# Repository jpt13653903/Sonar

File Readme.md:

# Sonar

Project used as a teaching aid for the [UCT FPGA course](https://github.com/jpt13653903/UCT-FPGA-Course).

## Overview

This DE10-Lite daughter card features transmitter and receiver array for a 10 kHz sonar system.

## Flexible Grid

The design features a 64-element grid of microphone sites and a connection matrix that supports 16 output channels.  The user can populate up to 16 microphones and then use the matrix to route them to the receiver channels.

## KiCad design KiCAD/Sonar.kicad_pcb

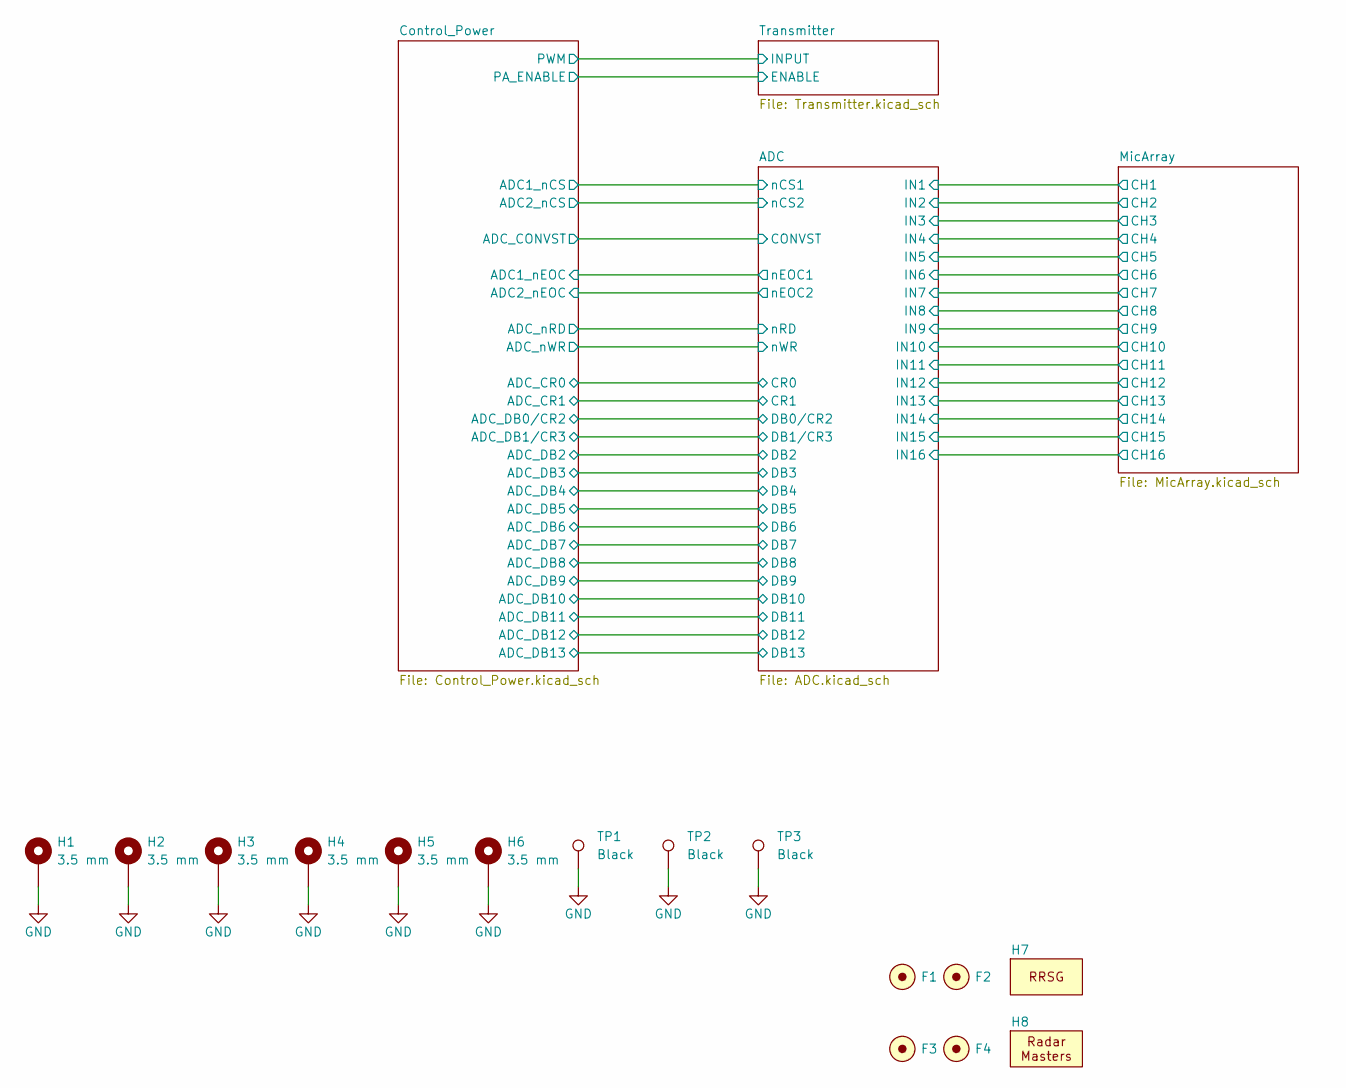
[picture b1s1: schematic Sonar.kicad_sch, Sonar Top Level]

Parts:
F1, F2, F3, F4: Fiducial_1mm_Mask3mm
H1, H2, H3, H4, H5, H6: MountingHole; MountingHole_3.5mm_Pad_Via
H7: RRSG
H8: RadarMasters
TP1, TP2, TP3: Keystone_5011_Black; TestPoint_Keystone_5010-5014_Multipurpose; MPN 5011

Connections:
GND: H1.1, H2.1, H3.1, H4.1, H5.1, H6.1, TP1.1 (1_1), TP2.1 (1_1), TP3.1 (1_1); also elsewhere on the board

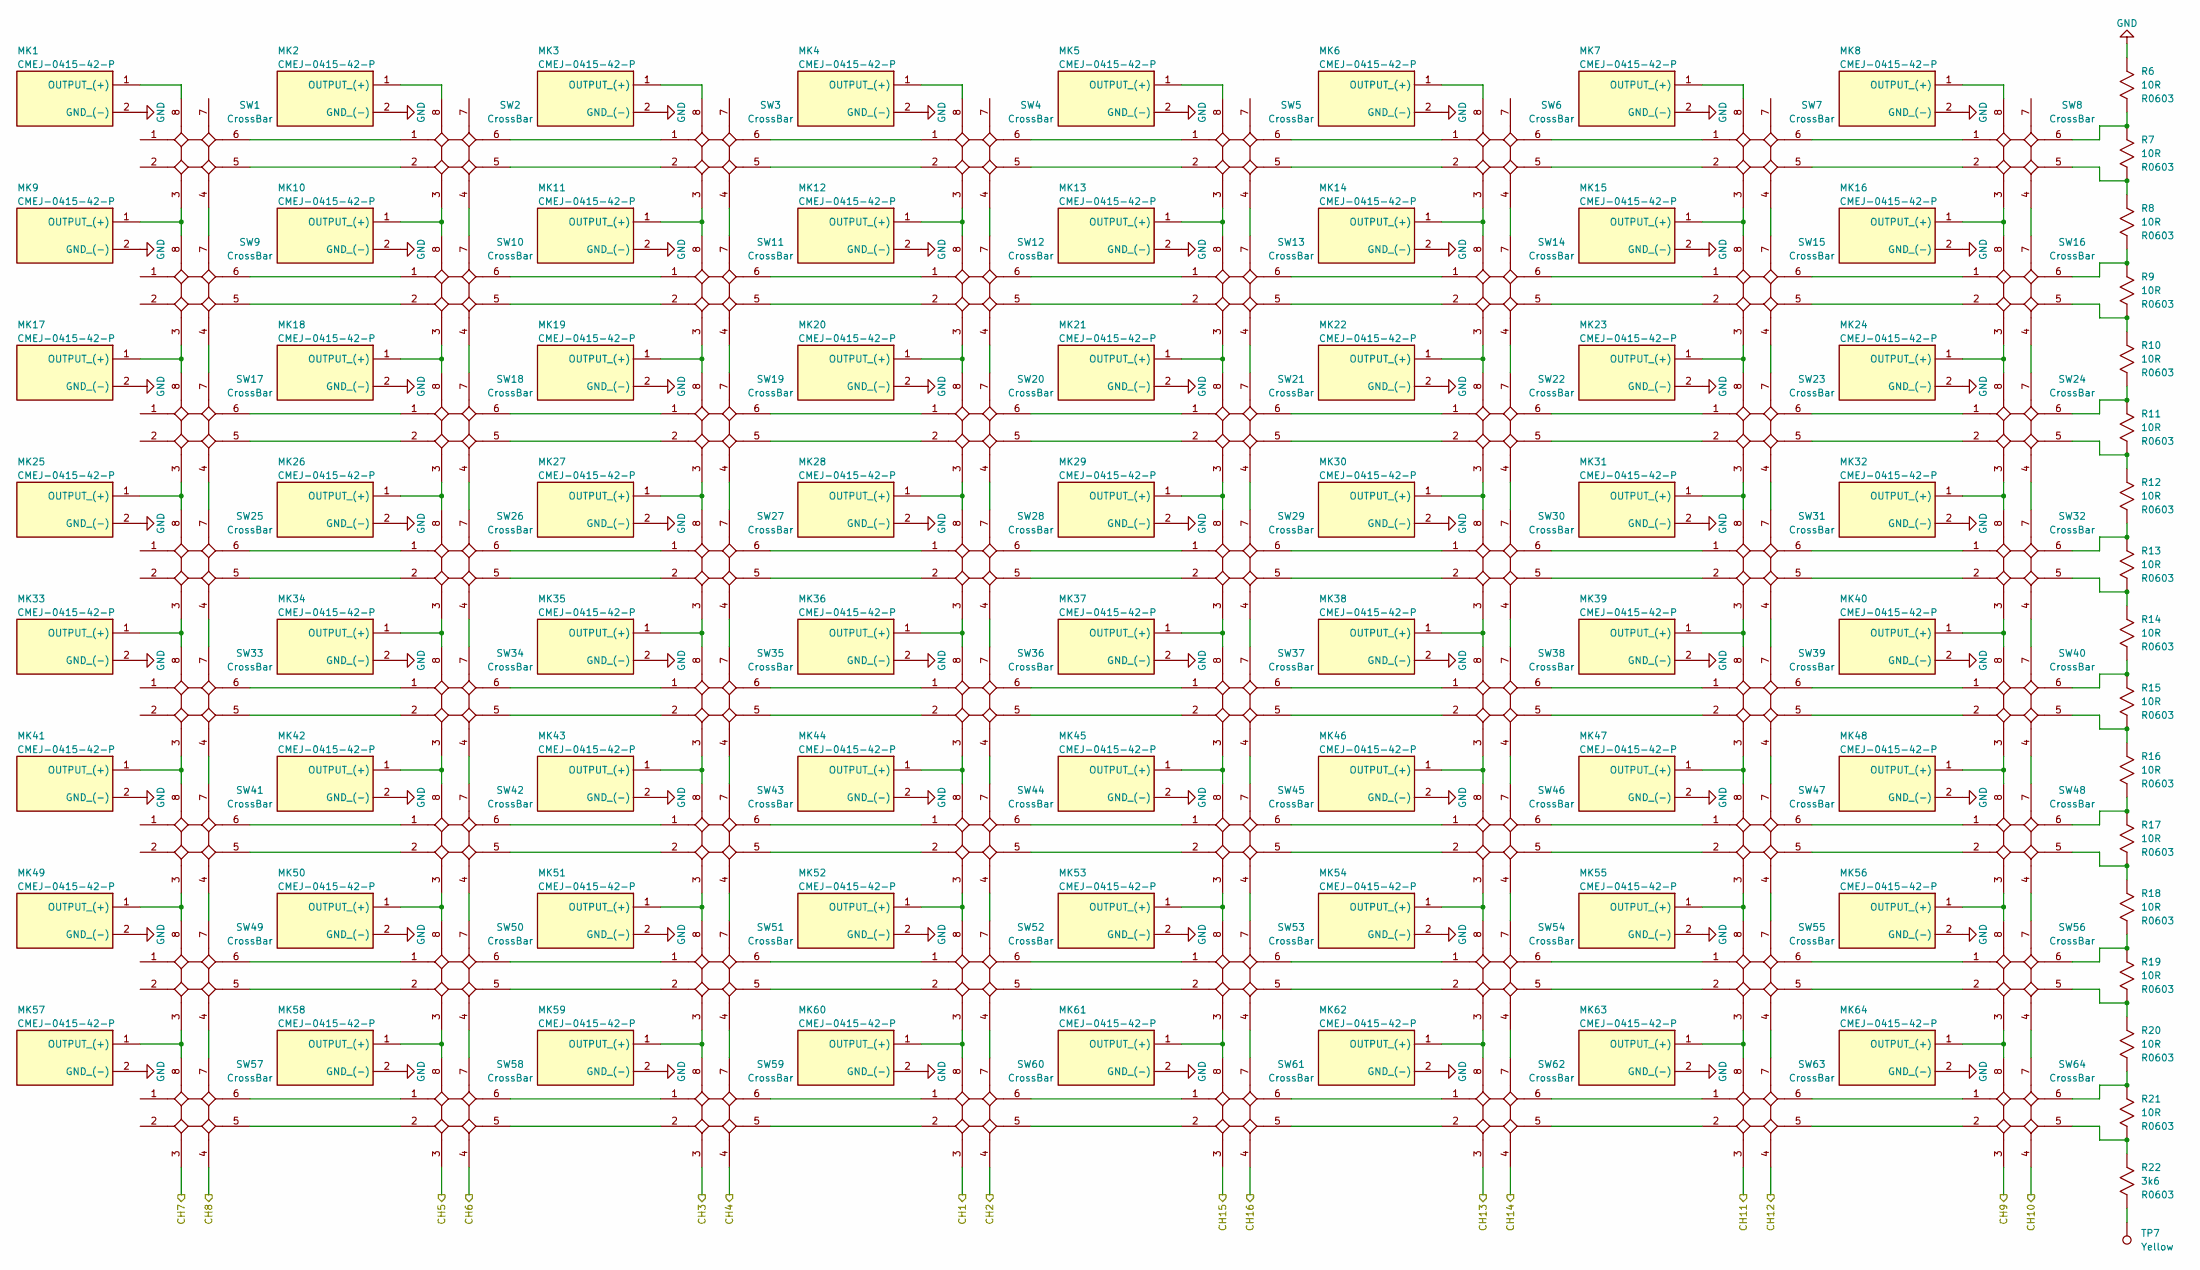
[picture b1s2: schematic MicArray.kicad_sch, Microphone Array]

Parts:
MK1, MK2, MK3, MK4, MK5, MK6, MK7, MK8, MK9, MK10, MK11, MK12, MK13, MK14, MK15, MK16, MK17, MK18, MK19, MK20, MK21, MK22, MK23, MK24, MK25, MK26, MK27, MK28, MK29, MK30, MK31, MK32, MK33, MK34, MK35, MK36, MK37, MK38, MK39, MK40, MK41, MK42, MK43, MK44, MK45, MK46, MK47, MK48, MK49, MK50, MK51, MK52, MK53, MK54, MK55, MK56, MK57, MK58, MK59, MK60, MK61, MK62, MK63, MK64: CMEJ-0415-42-P; CMEJ041542P; MPN CMEJ-0415-42-P
R6, R7, R8, R9, R10, R11, R12, R13, R14, R15, R16, R17, R18, R19, R20, R21: R0603_10R; R_0603_1608Metric; MPN CRGP0603F10R
R22: R0603_3k6; R_0603_1608Metric; MPN CRGP0603F3K6
SW1, SW2, SW3, SW4, SW5, SW6, SW7, SW8, SW9, SW10, SW11, SW12, SW13, SW14, SW15, SW16, SW17, SW18, SW19, SW20, SW21, SW22, SW23, SW24, SW25, SW26, SW27, SW28, SW29, SW30, SW31, SW32, SW33, SW34, SW35, SW36, SW37, SW38, SW39, SW40, SW41, SW42, SW43, SW44, SW45, SW46, SW47, SW48, SW49, SW50, SW51, SW52, SW53, SW54, SW55, SW56, SW57, SW58, SW59, SW60, SW61, SW62, SW63, SW64: CrossBar; CrossBar_2x2
TP7: Keystone_5014_Yellow; TestPoint_Keystone_5010-5014_Multipurpose; MPN 5014

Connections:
/ADC/IN1: SW60.3 (OUTPUT_(+)); also elsewhere on the board
/ADC/IN2: SW60.4 (GND_(-)); also elsewhere on the board
/ADC/IN3: SW59.3 (OUTPUT_(+)); also elsewhere on the board
/ADC/IN4: SW59.4 (GND_(-)); also elsewhere on the board
/ADC/IN5: SW58.3 (OUTPUT_(+)); also elsewhere on the board
/ADC/IN6: SW58.4 (GND_(-)); also elsewhere on the board
/ADC/IN7: SW57.3 (OUTPUT_(+)); also elsewhere on the board
/ADC/IN8: SW57.4 (GND_(-)); also elsewhere on the board
/ADC/IN9: SW64.3 (OUTPUT_(+)); also elsewhere on the board
/ADC/IN10: SW64.4 (GND_(-)); also elsewhere on the board
/ADC/IN11: SW63.3 (OUTPUT_(+)); also elsewhere on the board
/ADC/IN12: SW63.4 (GND_(-)); also elsewhere on the board
/ADC/IN13: SW62.3 (OUTPUT_(+)); also elsewhere on the board
/ADC/IN14: SW62.4 (GND_(-)); also elsewhere on the board
/ADC/IN15: SW61.3 (OUTPUT_(+)); also elsewhere on the board
/ADC/IN16: SW61.4 (GND_(-)); also elsewhere on the board
GND: MK1.2 (GND_(-)), MK2.2 (GND_(-)), MK3.2 (GND_(-)), MK4.2 (GND_(-)), MK5.2 (GND_(-)), MK6.2 (GND_(-)), MK7.2 (GND_(-)), MK8.2 (GND_(-)), MK9.2 (GND_(-)), MK10.2 (GND_(-)), MK11.2 (GND_(-)), MK12.2 (GND_(-)), MK13.2 (GND_(-)), MK14.2 (GND_(-)), MK15.2 (GND_(-)), MK16.2 (GND_(-)), MK17.2 (GND_(-)), MK18.2 (GND_(-)), MK19.2 (GND_(-)), MK20.2 (GND_(-)), MK21.2 (GND_(-)), MK22.2 (GND_(-)), MK23.2 (GND_(-)), MK24.2 (GND_(-)), MK25.2 (GND_(-)), MK26.2 (GND_(-)), MK27.2 (GND_(-)), MK28.2 (GND_(-)), MK29.2 (GND_(-)), MK30.2 (GND_(-)), MK31.2 (GND_(-)), MK32.2 (GND_(-)), MK33.2 (GND_(-)), MK34.2 (GND_(-)), MK35.2 (GND_(-)), MK36.2 (GND_(-)), MK37.2 (GND_(-)), MK38.2 (GND_(-)), MK39.2 (GND_(-)), MK40.2 (GND_(-)), MK41.2 (GND_(-)), MK42.2 (GND_(-)), MK43.2 (GND_(-)), MK44.2 (GND_(-)), MK45.2 (GND_(-)), MK46.2 (GND_(-)), MK47.2 (GND_(-)), MK48.2 (GND_(-)), MK49.2 (GND_(-)), MK50.2 (GND_(-)), MK51.2 (GND_(-)), MK52.2 (GND_(-)), MK53.2 (GND_(-)), MK54.2 (GND_(-)), MK55.2 (GND_(-)), MK56.2 (GND_(-)), MK57.2 (GND_(-)), MK58.2 (GND_(-)), MK59.2 (GND_(-)), MK60.2 (GND_(-)), MK61.2 (GND_(-)), MK62.2 (GND_(-)), MK63.2 (GND_(-)), MK64.2 (GND_(-)), R6.1; also elsewhere on the board
unnamed: MK1.1 (OUTPUT_(+)), SW1.8 (OUTPUT_(+))
unnamed: MK2.1 (OUTPUT_(+)), SW2.8 (OUTPUT_(+))
unnamed: MK3.1 (OUTPUT_(+)), SW3.8 (OUTPUT_(+))
unnamed: MK4.1 (OUTPUT_(+)), SW4.8 (OUTPUT_(+))
unnamed: MK5.1 (OUTPUT_(+)), SW5.8 (OUTPUT_(+))
unnamed: MK6.1 (OUTPUT_(+)), SW6.8 (OUTPUT_(+))
unnamed: MK7.1 (OUTPUT_(+)), SW7.8 (OUTPUT_(+))
unnamed: MK8.1 (OUTPUT_(+)), SW8.8 (OUTPUT_(+))
unnamed: MK9.1 (OUTPUT_(+)), SW1.3 (OUTPUT_(+)), SW9.8 (OUTPUT_(+))
unnamed: MK10.1 (OUTPUT_(+)), SW2.3 (OUTPUT_(+)), SW10.8 (OUTPUT_(+))
unnamed: MK11.1 (OUTPUT_(+)), SW3.3 (OUTPUT_(+)), SW11.8 (OUTPUT_(+))
unnamed: MK12.1 (OUTPUT_(+)), SW4.3 (OUTPUT_(+)), SW12.8 (OUTPUT_(+))
unnamed: MK13.1 (OUTPUT_(+)), SW5.3 (OUTPUT_(+)), SW13.8 (OUTPUT_(+))
unnamed: MK14.1 (OUTPUT_(+)), SW6.3 (OUTPUT_(+)), SW14.8 (OUTPUT_(+))
unnamed: MK15.1 (OUTPUT_(+)), SW7.3 (OUTPUT_(+)), SW15.8 (OUTPUT_(+))
unnamed: MK16.1 (OUTPUT_(+)), SW8.3 (OUTPUT_(+)), SW16.8 (OUTPUT_(+))
unnamed: MK17.1 (OUTPUT_(+)), SW9.3 (OUTPUT_(+)), SW17.8 (OUTPUT_(+))
unnamed: MK18.1 (OUTPUT_(+)), SW10.3 (OUTPUT_(+)), SW18.8 (OUTPUT_(+))
unnamed: MK19.1 (OUTPUT_(+)), SW11.3 (OUTPUT_(+)), SW19.8 (OUTPUT_(+))
unnamed: MK20.1 (OUTPUT_(+)), SW12.3 (OUTPUT_(+)), SW20.8 (OUTPUT_(+))
unnamed: MK21.1 (OUTPUT_(+)), SW13.3 (OUTPUT_(+)), SW21.8 (OUTPUT_(+))
unnamed: MK22.1 (OUTPUT_(+)), SW14.3 (OUTPUT_(+)), SW22.8 (OUTPUT_(+))
unnamed: MK23.1 (OUTPUT_(+)), SW15.3 (OUTPUT_(+)), SW23.8 (OUTPUT_(+))
unnamed: MK24.1 (OUTPUT_(+)), SW16.3 (OUTPUT_(+)), SW24.8 (OUTPUT_(+))
unnamed: MK25.1 (OUTPUT_(+)), SW17.3 (OUTPUT_(+)), SW25.8 (OUTPUT_(+))
unnamed: MK26.1 (OUTPUT_(+)), SW18.3 (OUTPUT_(+)), SW26.8 (OUTPUT_(+))
unnamed: MK27.1 (OUTPUT_(+)), SW19.3 (OUTPUT_(+)), SW27.8 (OUTPUT_(+))
unnamed: MK28.1 (OUTPUT_(+)), SW20.3 (OUTPUT_(+)), SW28.8 (OUTPUT_(+))
unnamed: MK29.1 (OUTPUT_(+)), SW21.3 (OUTPUT_(+)), SW29.8 (OUTPUT_(+))
unnamed: MK30.1 (OUTPUT_(+)), SW22.3 (OUTPUT_(+)), SW30.8 (OUTPUT_(+))
unnamed: MK31.1 (OUTPUT_(+)), SW23.3 (OUTPUT_(+)), SW31.8 (OUTPUT_(+))
unnamed: MK32.1 (OUTPUT_(+)), SW24.3 (OUTPUT_(+)), SW32.8 (OUTPUT_(+))
unnamed: MK33.1 (OUTPUT_(+)), SW25.3 (OUTPUT_(+)), SW33.8 (OUTPUT_(+))
unnamed: MK34.1 (OUTPUT_(+)), SW26.3 (OUTPUT_(+)), SW34.8 (OUTPUT_(+))
unnamed: MK35.1 (OUTPUT_(+)), SW27.3 (OUTPUT_(+)), SW35.8 (OUTPUT_(+))
unnamed: MK36.1 (OUTPUT_(+)), SW28.3 (OUTPUT_(+)), SW36.8 (OUTPUT_(+))
unnamed: MK37.1 (OUTPUT_(+)), SW29.3 (OUTPUT_(+)), SW37.8 (OUTPUT_(+))
unnamed: MK38.1 (OUTPUT_(+)), SW30.3 (OUTPUT_(+)), SW38.8 (OUTPUT_(+))
unnamed: MK39.1 (OUTPUT_(+)), SW31.3 (OUTPUT_(+)), SW39.8 (OUTPUT_(+))
unnamed: MK40.1 (OUTPUT_(+)), SW32.3 (OUTPUT_(+)), SW40.8 (OUTPUT_(+))
unnamed: MK41.1 (OUTPUT_(+)), SW33.3 (OUTPUT_(+)), SW41.8 (OUTPUT_(+))
unnamed: MK42.1 (OUTPUT_(+)), SW34.3 (OUTPUT_(+)), SW42.8 (OUTPUT_(+))
unnamed: MK43.1 (OUTPUT_(+)), SW35.3 (OUTPUT_(+)), SW43.8 (OUTPUT_(+))
unnamed: MK44.1 (OUTPUT_(+)), SW36.3 (OUTPUT_(+)), SW44.8 (OUTPUT_(+))
unnamed: MK45.1 (OUTPUT_(+)), SW37.3 (OUTPUT_(+)), SW45.8 (OUTPUT_(+))
unnamed: MK46.1 (OUTPUT_(+)), SW38.3 (OUTPUT_(+)), SW46.8 (OUTPUT_(+))
unnamed: MK47.1 (OUTPUT_(+)), SW39.3 (OUTPUT_(+)), SW47.8 (OUTPUT_(+))
unnamed: MK48.1 (OUTPUT_(+)), SW40.3 (OUTPUT_(+)), SW48.8 (OUTPUT_(+))
unnamed: MK49.1 (OUTPUT_(+)), SW41.3 (OUTPUT_(+)), SW49.8 (OUTPUT_(+))
unnamed: MK50.1 (OUTPUT_(+)), SW42.3 (OUTPUT_(+)), SW50.8 (OUTPUT_(+))
unnamed: MK51.1 (OUTPUT_(+)), SW43.3 (OUTPUT_(+)), SW51.8 (OUTPUT_(+))
unnamed: MK52.1 (OUTPUT_(+)), SW44.3 (OUTPUT_(+)), SW52.8 (OUTPUT_(+))
unnamed: MK53.1 (OUTPUT_(+)), SW45.3 (OUTPUT_(+)), SW53.8 (OUTPUT_(+))
unnamed: MK54.1 (OUTPUT_(+)), SW46.3 (OUTPUT_(+)), SW54.8 (OUTPUT_(+))
unnamed: MK55.1 (OUTPUT_(+)), SW47.3 (OUTPUT_(+)), SW55.8 (OUTPUT_(+))
unnamed: MK56.1 (OUTPUT_(+)), SW48.3 (OUTPUT_(+)), SW56.8 (OUTPUT_(+))
unnamed: MK57.1 (OUTPUT_(+)), SW49.3 (OUTPUT_(+)), SW57.8 (OUTPUT_(+))
unnamed: MK58.1 (OUTPUT_(+)), SW50.3 (OUTPUT_(+)), SW58.8 (OUTPUT_(+))
unnamed: MK59.1 (OUTPUT_(+)), SW51.3 (OUTPUT_(+)), SW59.8 (OUTPUT_(+))
unnamed: MK60.1 (OUTPUT_(+)), SW52.3 (OUTPUT_(+)), SW60.8 (OUTPUT_(+))
unnamed: MK61.1 (OUTPUT_(+)), SW53.3 (OUTPUT_(+)), SW61.8 (OUTPUT_(+))
unnamed: MK62.1 (OUTPUT_(+)), SW54.3 (OUTPUT_(+)), SW62.8 (OUTPUT_(+))
unnamed: MK63.1 (OUTPUT_(+)), SW55.3 (OUTPUT_(+)), SW63.8 (OUTPUT_(+))
unnamed: MK64.1 (OUTPUT_(+)), SW56.3 (OUTPUT_(+)), SW64.8 (OUTPUT_(+))
unnamed: R6.2, R7.1, SW8.6 (OUTPUT_(+))
unnamed: R7.2, R8.1, SW8.5 (GND_(-))
unnamed: R8.2, R9.1, SW16.6 (OUTPUT_(+))
unnamed: R9.2, R10.1, SW16.5 (GND_(-))
unnamed: R10.2, R11.1, SW24.6 (OUTPUT_(+))
unnamed: R11.2, R12.1, SW24.5 (GND_(-))
unnamed: R12.2, R13.1, SW32.6 (OUTPUT_(+))
unnamed: R13.2, R14.1, SW32.5 (GND_(-))
unnamed: R14.2, R15.1, SW40.6 (OUTPUT_(+))
unnamed: R15.2, R16.1, SW40.5 (GND_(-))
unnamed: R16.2, R17.1, SW48.6 (OUTPUT_(+))
unnamed: R17.2, R18.1, SW48.5 (GND_(-))
unnamed: R18.2, R19.1, SW56.6 (OUTPUT_(+))
unnamed: R19.2, R20.1, SW56.5 (GND_(-))
unnamed: R20.2, R21.1, SW64.6 (OUTPUT_(+))
unnamed: R21.2, R22.1, SW64.5 (GND_(-))
unnamed: R22.2, TP7.1 (1_1)
unnamed: SW1.4 (GND_(-)), SW9.7 (GND_(-))
unnamed: SW1.5 (GND_(-)), SW2.2 (GND_(-))
unnamed: SW1.6 (OUTPUT_(+)), SW2.1 (OUTPUT_(+))
unnamed: SW2.5 (GND_(-)), SW3.2 (GND_(-))
unnamed: SW2.6 (OUTPUT_(+)), SW3.1 (OUTPUT_(+))
unnamed: SW3.5 (GND_(-)), SW4.2 (GND_(-))
unnamed: SW3.6 (OUTPUT_(+)), SW4.1 (OUTPUT_(+))
unnamed: SW4.5 (GND_(-)), SW5.2 (GND_(-))
unnamed: SW4.6 (OUTPUT_(+)), SW5.1 (OUTPUT_(+))
unnamed: SW5.5 (GND_(-)), SW6.2 (GND_(-))
unnamed: SW5.6 (OUTPUT_(+)), SW6.1 (OUTPUT_(+))
unnamed: SW6.5 (GND_(-)), SW7.2 (GND_(-))
unnamed: SW6.6 (OUTPUT_(+)), SW7.1 (OUTPUT_(+))
unnamed: SW7.5 (GND_(-)), SW8.2 (GND_(-))
unnamed: SW7.6 (OUTPUT_(+)), SW8.1 (OUTPUT_(+))
unnamed: SW9.5 (GND_(-)), SW10.2 (GND_(-))
unnamed: SW10.4 (GND_(-)), SW18.7 (GND_(-))
unnamed: SW10.5 (GND_(-)), SW11.2 (GND_(-))
unnamed: SW2.4 (GND_(-)), SW10.7 (GND_(-))
unnamed: SW9.6 (OUTPUT_(+)), SW10.1 (OUTPUT_(+))
unnamed: SW10.6 (OUTPUT_(+)), SW11.1 (OUTPUT_(+))
unnamed: SW11.4 (GND_(-)), SW19.7 (GND_(-))
unnamed: SW11.5 (GND_(-)), SW12.2 (GND_(-))
unnamed: SW3.4 (GND_(-)), SW11.7 (GND_(-))
unnamed: SW11.6 (OUTPUT_(+)), SW12.1 (OUTPUT_(+))
unnamed: SW12.4 (GND_(-)), SW20.7 (GND_(-))
unnamed: SW12.5 (GND_(-)), SW13.2 (GND_(-))
unnamed: SW4.4 (GND_(-)), SW12.7 (GND_(-))
unnamed: SW12.6 (OUTPUT_(+)), SW13.1 (OUTPUT_(+))
unnamed: SW13.4 (GND_(-)), SW21.7 (GND_(-))
unnamed: SW13.5 (GND_(-)), SW14.2 (GND_(-))
unnamed: SW5.4 (GND_(-)), SW13.7 (GND_(-))
unnamed: SW13.6 (OUTPUT_(+)), SW14.1 (OUTPUT_(+))
unnamed: SW14.4 (GND_(-)), SW22.7 (GND_(-))
unnamed: SW14.5 (GND_(-)), SW15.2 (GND_(-))
unnamed: SW6.4 (GND_(-)), SW14.7 (GND_(-))
unnamed: SW14.6 (OUTPUT_(+)), SW15.1 (OUTPUT_(+))
unnamed: SW15.4 (GND_(-)), SW23.7 (GND_(-))
unnamed: SW15.5 (GND_(-)), SW16.2 (GND_(-))
unnamed: SW7.4 (GND_(-)), SW15.7 (GND_(-))
unnamed: SW15.6 (OUTPUT_(+)), SW16.1 (OUTPUT_(+))
unnamed: SW16.4 (GND_(-)), SW24.7 (GND_(-))
unnamed: SW8.4 (GND_(-)), SW16.7 (GND_(-))
unnamed: SW17.4 (GND_(-)), SW25.7 (GND_(-))
unnamed: SW17.5 (GND_(-)), SW18.2 (GND_(-))
unnamed: SW9.4 (GND_(-)), SW17.7 (GND_(-))
unnamed: SW17.6 (OUTPUT_(+)), SW18.1 (OUTPUT_(+))
unnamed: SW18.4 (GND_(-)), SW26.7 (GND_(-))
unnamed: SW18.5 (GND_(-)), SW19.2 (GND_(-))
unnamed: SW18.6 (OUTPUT_(+)), SW19.1 (OUTPUT_(+))
unnamed: SW19.4 (GND_(-)), SW27.7 (GND_(-))
unnamed: SW19.5 (GND_(-)), SW20.2 (GND_(-))
unnamed: SW19.6 (OUTPUT_(+)), SW20.1 (OUTPUT_(+))
unnamed: SW20.4 (GND_(-)), SW28.7 (GND_(-))
unnamed: SW20.5 (GND_(-)), SW21.2 (GND_(-))
unnamed: SW20.6 (OUTPUT_(+)), SW21.1 (OUTPUT_(+))
unnamed: SW21.4 (GND_(-)), SW29.7 (GND_(-))
unnamed: SW21.5 (GND_(-)), SW22.2 (GND_(-))
unnamed: SW21.6 (OUTPUT_(+)), SW22.1 (OUTPUT_(+))
unnamed: SW22.4 (GND_(-)), SW30.7 (GND_(-))
unnamed: SW22.5 (GND_(-)), SW23.2 (GND_(-))
unnamed: SW22.6 (OUTPUT_(+)), SW23.1 (OUTPUT_(+))
unnamed: SW23.4 (GND_(-)), SW31.7 (GND_(-))
unnamed: SW23.5 (GND_(-)), SW24.2 (GND_(-))
unnamed: SW23.6 (OUTPUT_(+)), SW24.1 (OUTPUT_(+))
unnamed: SW24.4 (GND_(-)), SW32.7 (GND_(-))
unnamed: SW25.4 (GND_(-)), SW33.7 (GND_(-))
unnamed: SW25.5 (GND_(-)), SW26.2 (GND_(-))
unnamed: SW25.6 (OUTPUT_(+)), SW26.1 (OUTPUT_(+))
unnamed: SW26.4 (GND_(-)), SW34.7 (GND_(-))
unnamed: SW26.5 (GND_(-)), SW27.2 (GND_(-))
unnamed: SW26.6 (OUTPUT_(+)), SW27.1 (OUTPUT_(+))
unnamed: SW27.4 (GND_(-)), SW35.7 (GND_(-))
unnamed: SW27.5 (GND_(-)), SW28.2 (GND_(-))
unnamed: SW27.6 (OUTPUT_(+)), SW28.1 (OUTPUT_(+))
unnamed: SW28.4 (GND_(-)), SW36.7 (GND_(-))
unnamed: SW28.5 (GND_(-)), SW29.2 (GND_(-))
unnamed: SW28.6 (OUTPUT_(+)), SW29.1 (OUTPUT_(+))
unnamed: SW29.4 (GND_(-)), SW37.7 (GND_(-))
unnamed: SW29.5 (GND_(-)), SW30.2 (GND_(-))
unnamed: SW29.6 (OUTPUT_(+)), SW30.1 (OUTPUT_(+))
unnamed: SW30.4 (GND_(-)), SW38.7 (GND_(-))
unnamed: SW30.5 (GND_(-)), SW31.2 (GND_(-))
unnamed: SW30.6 (OUTPUT_(+)), SW31.1 (OUTPUT_(+))
unnamed: SW31.4 (GND_(-)), SW39.7 (GND_(-))
unnamed: SW31.5 (GND_(-)), SW32.2 (GND_(-))
unnamed: SW31.6 (OUTPUT_(+)), SW32.1 (OUTPUT_(+))
unnamed: SW32.4 (GND_(-)), SW40.7 (GND_(-))
unnamed: SW33.4 (GND_(-)), SW41.7 (GND_(-))
unnamed: SW33.5 (GND_(-)), SW34.2 (GND_(-))
unnamed: SW33.6 (OUTPUT_(+)), SW34.1 (OUTPUT_(+))
unnamed: SW34.4 (GND_(-)), SW42.7 (GND_(-))
unnamed: SW34.5 (GND_(-)), SW35.2 (GND_(-))
unnamed: SW34.6 (OUTPUT_(+)), SW35.1 (OUTPUT_(+))
unnamed: SW35.4 (GND_(-)), SW43.7 (GND_(-))
unnamed: SW35.5 (GND_(-)), SW36.2 (GND_(-))
unnamed: SW35.6 (OUTPUT_(+)), SW36.1 (OUTPUT_(+))
unnamed: SW36.4 (GND_(-)), SW44.7 (GND_(-))
unnamed: SW36.5 (GND_(-)), SW37.2 (GND_(-))
unnamed: SW36.6 (OUTPUT_(+)), SW37.1 (OUTPUT_(+))
unnamed: SW37.4 (GND_(-)), SW45.7 (GND_(-))
unnamed: SW37.5 (GND_(-)), SW38.2 (GND_(-))
unnamed: SW37.6 (OUTPUT_(+)), SW38.1 (OUTPUT_(+))
unnamed: SW38.4 (GND_(-)), SW46.7 (GND_(-))
unnamed: SW38.5 (GND_(-)), SW39.2 (GND_(-))
unnamed: SW38.6 (OUTPUT_(+)), SW39.1 (OUTPUT_(+))
unnamed: SW39.4 (GND_(-)), SW47.7 (GND_(-))
unnamed: SW39.5 (GND_(-)), SW40.2 (GND_(-))
unnamed: SW39.6 (OUTPUT_(+)), SW40.1 (OUTPUT_(+))
unnamed: SW40.4 (GND_(-)), SW48.7 (GND_(-))
unnamed: SW41.4 (GND_(-)), SW49.7 (GND_(-))
unnamed: SW41.5 (GND_(-)), SW42.2 (GND_(-))
unnamed: SW41.6 (OUTPUT_(+)), SW42.1 (OUTPUT_(+))
unnamed: SW42.4 (GND_(-)), SW50.7 (GND_(-))
unnamed: SW42.5 (GND_(-)), SW43.2 (GND_(-))
unnamed: SW42.6 (OUTPUT_(+)), SW43.1 (OUTPUT_(+))
unnamed: SW43.4 (GND_(-)), SW51.7 (GND_(-))
unnamed: SW43.5 (GND_(-)), SW44.2 (GND_(-))
unnamed: SW43.6 (OUTPUT_(+)), SW44.1 (OUTPUT_(+))
unnamed: SW44.4 (GND_(-)), SW52.7 (GND_(-))
unnamed: SW44.5 (GND_(-)), SW45.2 (GND_(-))
unnamed: SW44.6 (OUTPUT_(+)), SW45.1 (OUTPUT_(+))
unnamed: SW45.4 (GND_(-)), SW53.7 (GND_(-))
unnamed: SW45.5 (GND_(-)), SW46.2 (GND_(-))
unnamed: SW45.6 (OUTPUT_(+)), SW46.1 (OUTPUT_(+))
unnamed: SW46.4 (GND_(-)), SW54.7 (GND_(-))
unnamed: SW46.5 (GND_(-)), SW47.2 (GND_(-))
unnamed: SW46.6 (OUTPUT_(+)), SW47.1 (OUTPUT_(+))
unnamed: SW47.4 (GND_(-)), SW55.7 (GND_(-))
unnamed: SW47.5 (GND_(-)), SW48.2 (GND_(-))
unnamed: SW47.6 (OUTPUT_(+)), SW48.1 (OUTPUT_(+))
unnamed: SW48.4 (GND_(-)), SW56.7 (GND_(-))
unnamed: SW49.4 (GND_(-)), SW57.7 (GND_(-))
unnamed: SW49.5 (GND_(-)), SW50.2 (GND_(-))
unnamed: SW49.6 (OUTPUT_(+)), SW50.1 (OUTPUT_(+))
unnamed: SW50.4 (GND_(-)), SW58.7 (GND_(-))
unnamed: SW50.5 (GND_(-)), SW51.2 (GND_(-))
unnamed: SW50.6 (OUTPUT_(+)), SW51.1 (OUTPUT_(+))
unnamed: SW51.4 (GND_(-)), SW59.7 (GND_(-))
unnamed: SW51.5 (GND_(-)), SW52.2 (GND_(-))
unnamed: SW51.6 (OUTPUT_(+)), SW52.1 (OUTPUT_(+))
unnamed: SW52.4 (GND_(-)), SW60.7 (GND_(-))
unnamed: SW52.5 (GND_(-)), SW53.2 (GND_(-))
unnamed: SW52.6 (OUTPUT_(+)), SW53.1 (OUTPUT_(+))
unnamed: SW53.4 (GND_(-)), SW61.7 (GND_(-))
unnamed: SW53.5 (GND_(-)), SW54.2 (GND_(-))
unnamed: SW53.6 (OUTPUT_(+)), SW54.1 (OUTPUT_(+))
unnamed: SW54.4 (GND_(-)), SW62.7 (GND_(-))
unnamed: SW54.5 (GND_(-)), SW55.2 (GND_(-))
unnamed: SW54.6 (OUTPUT_(+)), SW55.1 (OUTPUT_(+))
unnamed: SW55.4 (GND_(-)), SW63.7 (GND_(-))
unnamed: SW55.5 (GND_(-)), SW56.2 (GND_(-))
unnamed: SW55.6 (OUTPUT_(+)), SW56.1 (OUTPUT_(+))
unnamed: SW56.4 (GND_(-)), SW64.7 (GND_(-))
unnamed: SW57.5 (GND_(-)), SW58.2 (GND_(-))
unnamed: SW57.6 (OUTPUT_(+)), SW58.1 (OUTPUT_(+))
unnamed: SW58.5 (GND_(-)), SW59.2 (GND_(-))
unnamed: SW58.6 (OUTPUT_(+)), SW59.1 (OUTPUT_(+))
unnamed: SW59.5 (GND_(-)), SW60.2 (GND_(-))
unnamed: SW59.6 (OUTPUT_(+)), SW60.1 (OUTPUT_(+))
unnamed: SW60.5 (GND_(-)), SW61.2 (GND_(-))
unnamed: SW60.6 (OUTPUT_(+)), SW61.1 (OUTPUT_(+))
unnamed: SW61.5 (GND_(-)), SW62.2 (GND_(-))
unnamed: SW61.6 (OUTPUT_(+)), SW62.1 (OUTPUT_(+))
unnamed: SW62.5 (GND_(-)), SW63.2 (GND_(-))
unnamed: SW62.6 (OUTPUT_(+)), SW63.1 (OUTPUT_(+))
unnamed: SW63.5 (GND_(-)), SW64.2 (GND_(-))
unnamed: SW63.6 (OUTPUT_(+)), SW64.1 (OUTPUT_(+))

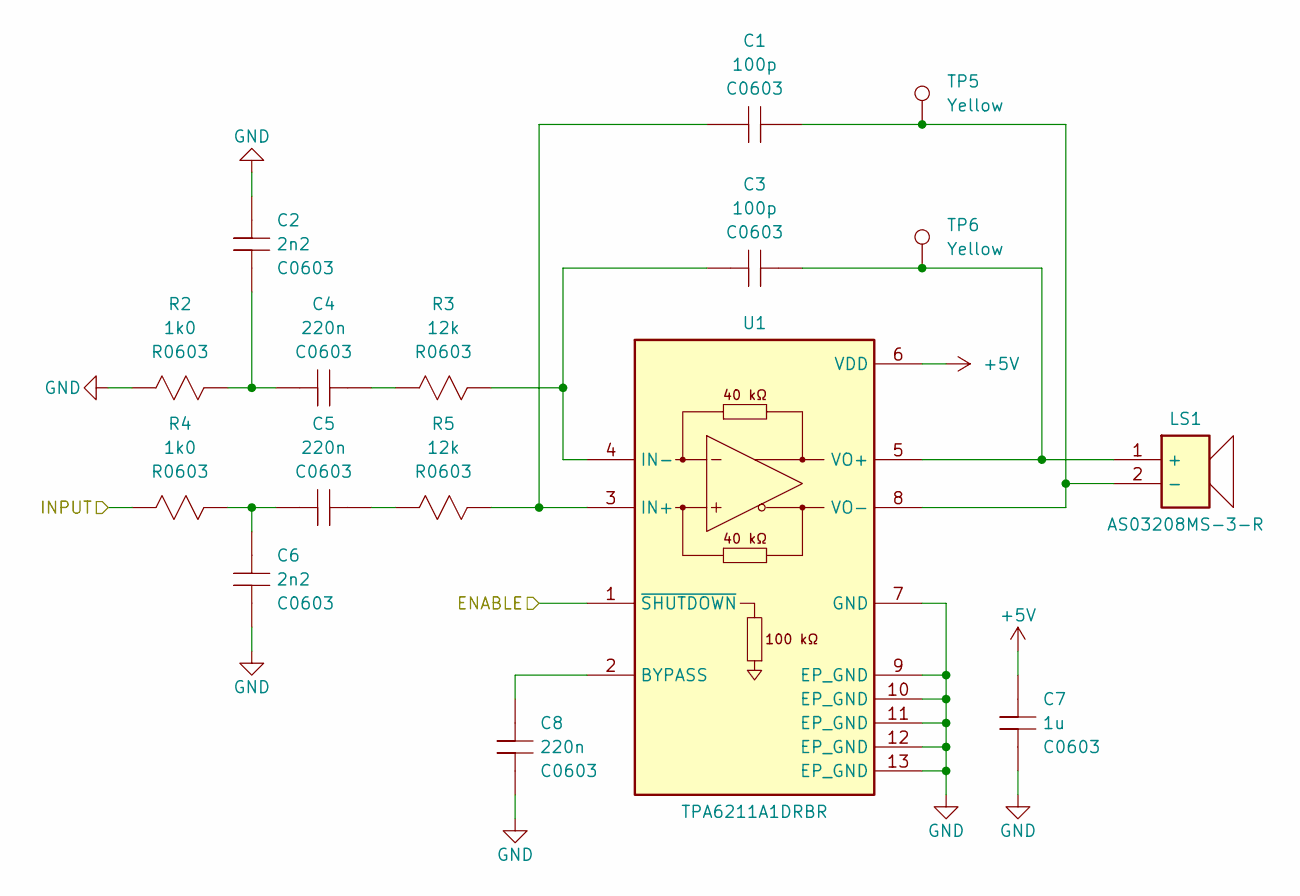
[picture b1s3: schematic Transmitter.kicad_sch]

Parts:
C1, C3: C0603_100p; C_0603_1608Metric; MPN GCG1885G1H101JA01D
C2, C6: C0603_2n2; C_0603_1608Metric; MPN GRM1885C1H222JA01D
C4, C5, C8: C0603_220n; C_0603_1608Metric; MPN GCM188R71E224MA55J
C7: C0603_1u0; C_0603_1608Metric; MPN GRT188R61H105KE13D
LS1: AS03208MS-3-R; MPN AS03208MS-3-R
R2, R4: R0603_1k0; R_0603_1608Metric; MPN CRGP0603F1K0
R3, R5: R0603_12k; R_0603_1608Metric; MPN CRGP0603F12K
TP5, TP6: Keystone_5014_Yellow; TestPoint_Keystone_5010-5014_Multipurpose; MPN 5014
U1: TPA6211A1DRBR; TPS73719QDRBRQ1; MPN TPA6211A1DRBR

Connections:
+5V: C7.1, U1.6 (VDD); also elsewhere on the board
/Control_Power/PA_ENABLE: U1.1 (~SHUTDOWN); also elsewhere on the board
/Control_Power/PWM: R4.1; also elsewhere on the board
GND: C2.1, C6.2, C7.2, C8.2, R2.1, U1.7 (GND), U1.9 (EP_GND), U1.10 (EP_GND), U1.11 (EP_GND), U1.12 (EP_GND), U1.13 (EP_GND); also elsewhere on the board
unnamed: C2.2, C4.1, R2.2
unnamed: C4.2, R3.1
unnamed: C5.1, C6.1, R4.2
unnamed: C5.2, R5.1
unnamed: C3.2, LS1.1 (+), TP6.1 (1_1), U1.5 (VO+)
unnamed: C1.2, LS1.2 (-), TP5.1 (1_1), U1.8 (VO-)
unnamed: C8.1, U1.2 (BYPASS)
unnamed: C1.1, R5.2, U1.3 (IN+)
unnamed: C3.1, R3.2, U1.4 (IN-)

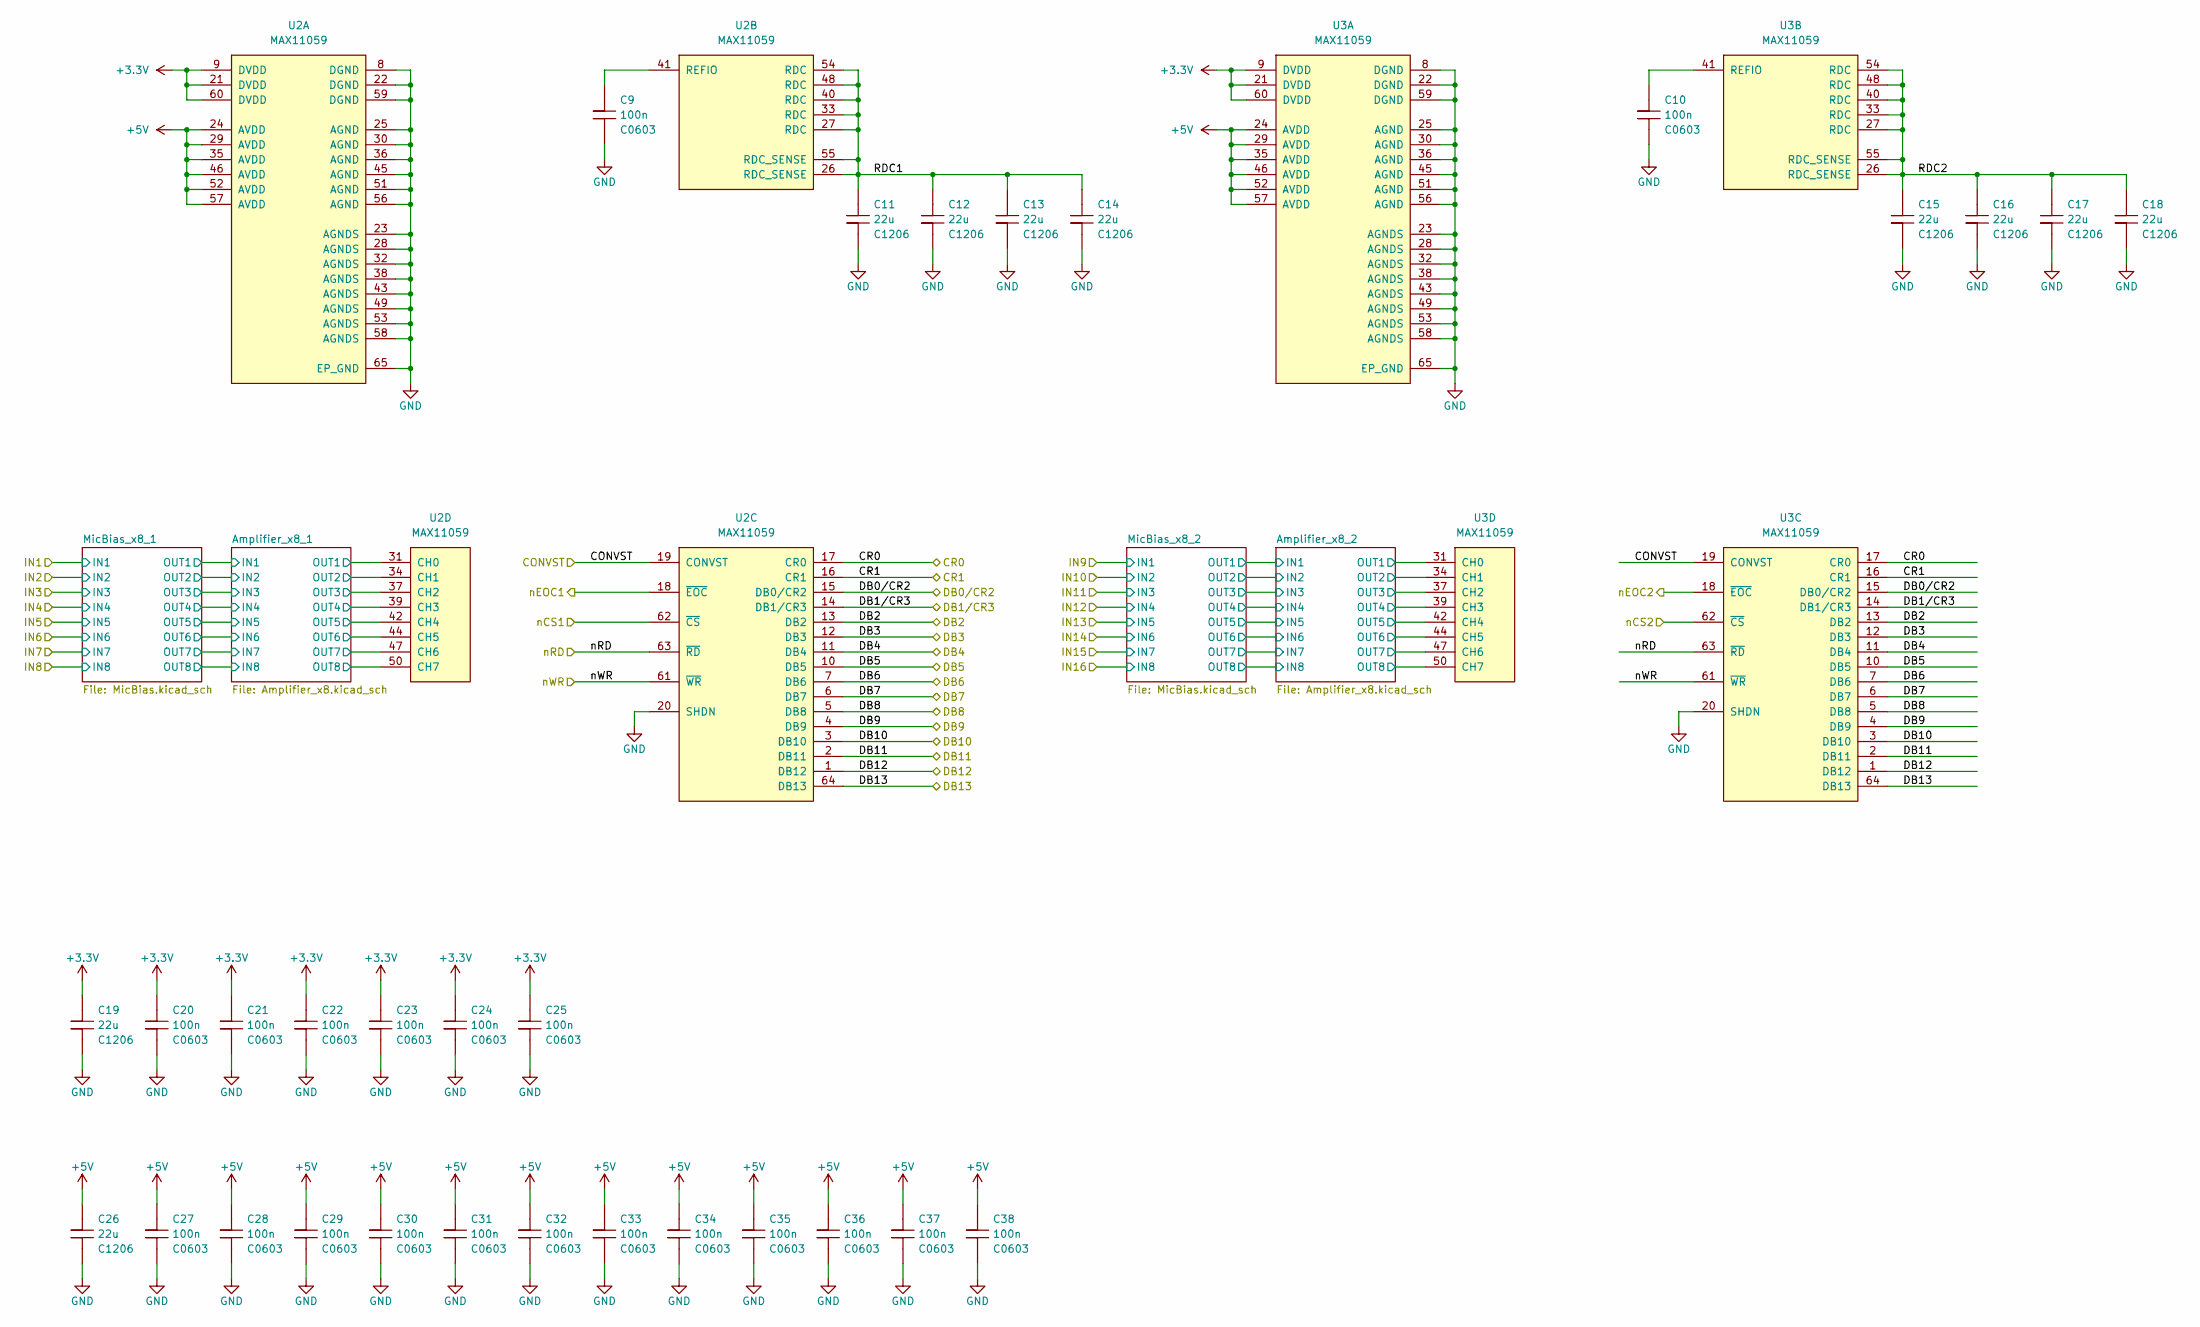
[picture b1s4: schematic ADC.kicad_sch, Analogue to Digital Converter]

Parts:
C9, C10, C20, C21, C22, C23, C24, C25, C27, C28, C29, C30, C31, C32, C33, C34, C35, C36, C37, C38: C0603_100n; C_0603_1608Metric; MPN GCG188R91H104KA01D
C11, C12, C13, C14, C15, C16, C17, C18, C19, C26: C1206_22u; C_1206_3216Metric; MPN C1206C226M4PACTU
U2, U3: MAX11059; Texas_TQFP-64-1EP_10x10mm_P0.5mm_EP8x8mm_Mask5x5mm; MPN MAX11059ECB+

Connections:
+3.3V: C19.1, C20.1, C21.1, C22.1, C23.1, C24.1, C25.1, U2.9 (DVDD), U2.21 (DVDD), U2.60 (DVDD), U3.9 (DVDD), U3.21 (DVDD), U3.60 (DVDD); also elsewhere on the board
+5V: C26.1, C27.1, C28.1, C29.1, C30.1, C31.1, C32.1, C33.1, C34.1, C35.1, C36.1, C37.1, C38.1, U2.24 (AVDD), U2.29 (AVDD), U2.35 (AVDD), U2.46 (AVDD), U2.52 (AVDD), U2.57 (AVDD), U3.24 (AVDD), U3.29 (AVDD), U3.35 (AVDD), U3.46 (AVDD), U3.52 (AVDD), U3.57 (AVDD); also elsewhere on the board
/ADC/Amplifier_x8_1/OUT1: U2.31 (CH0); also elsewhere on the board
/ADC/Amplifier_x8_1/OUT2: U2.34 (CH1); also elsewhere on the board
/ADC/Amplifier_x8_1/OUT3: U2.37 (CH2); also elsewhere on the board
/ADC/Amplifier_x8_1/OUT4: U2.39 (CH3); also elsewhere on the board
/ADC/Amplifier_x8_1/OUT5: U2.42 (CH4); also elsewhere on the board
/ADC/Amplifier_x8_1/OUT6: U2.44 (CH5); also elsewhere on the board
/ADC/Amplifier_x8_1/OUT7: U2.47 (CH6); also elsewhere on the board
/ADC/Amplifier_x8_1/OUT8: U2.50 (CH7); also elsewhere on the board
/ADC/Amplifier_x8_2/OUT1: U3.31 (CH0); also elsewhere on the board
/ADC/Amplifier_x8_2/OUT2: U3.34 (CH1); also elsewhere on the board
/ADC/Amplifier_x8_2/OUT3: U3.37 (CH2); also elsewhere on the board
/ADC/Amplifier_x8_2/OUT4: U3.39 (CH3); also elsewhere on the board
/ADC/Amplifier_x8_2/OUT5: U3.42 (CH4); also elsewhere on the board
/ADC/Amplifier_x8_2/OUT6: U3.44 (CH5); also elsewhere on the board
/ADC/Amplifier_x8_2/OUT7: U3.47 (CH6); also elsewhere on the board
/ADC/Amplifier_x8_2/OUT8: U3.50 (CH7); also elsewhere on the board
/ADC/CONVST: U2.19 (CONVST), U3.19 (CONVST); also elsewhere on the board
/ADC/CR0: U2.17 (CR0), U3.17 (CR0); also elsewhere on the board
/ADC/CR1: U2.16 (CR1), U3.16 (CR1); also elsewhere on the board
/ADC/DB0/CR2: U2.15 (DB0/CR2), U3.15 (DB0/CR2); also elsewhere on the board
/ADC/DB1/CR3: U2.14 (DB1/CR3), U3.14 (DB1/CR3); also elsewhere on the board
/ADC/DB2: U2.13 (DB2), U3.13 (DB2); also elsewhere on the board
/ADC/DB3: U2.12 (DB3), U3.12 (DB3); also elsewhere on the board
/ADC/DB4: U2.11 (DB4), U3.11 (DB4); also elsewhere on the board
/ADC/DB5: U2.10 (DB5), U3.10 (DB5); also elsewhere on the board
/ADC/DB6: U2.7 (DB6), U3.7 (DB6); also elsewhere on the board
/ADC/DB7: U2.6 (DB7), U3.6 (DB7); also elsewhere on the board
/ADC/DB8: U2.5 (DB8), U3.5 (DB8); also elsewhere on the board
/ADC/DB9: U2.4 (DB9), U3.4 (DB9); also elsewhere on the board
/ADC/DB10: U2.3 (DB10), U3.3 (DB10); also elsewhere on the board
/ADC/DB11: U2.2 (DB11), U3.2 (DB11); also elsewhere on the board
/ADC/DB12: U2.1 (DB12), U3.1 (DB12); also elsewhere on the board
/ADC/DB13: U2.64 (DB13), U3.64 (DB13); also elsewhere on the board
/ADC/RDC1: C11.1, C12.1, C13.1, C14.1, U2.26 (RDC_SENSE), U2.27 (RDC), U2.33 (RDC), U2.40 (RDC), U2.48 (RDC), U2.54 (RDC), U2.55 (RDC_SENSE)
/ADC/RDC2: C15.1, C16.1, C17.1, C18.1, U3.26 (RDC_SENSE), U3.27 (RDC), U3.33 (RDC), U3.40 (RDC), U3.48 (RDC), U3.54 (RDC), U3.55 (RDC_SENSE)
/ADC/nCS1: U2.62 (~CS); also elsewhere on the board
/ADC/nCS2: U3.62 (~CS); also elsewhere on the board
/ADC/nEOC1: U2.18 (~EOC); also elsewhere on the board
/ADC/nEOC2: U3.18 (~EOC); also elsewhere on the board
/ADC/nRD: U2.63 (~RD), U3.63 (~RD); also elsewhere on the board
/ADC/nWR: U2.61 (~WR), U3.61 (~WR); also elsewhere on the board
GND: C9.2, C10.2, C11.2, C12.2, C13.2, C14.2, C15.2, C16.2, C17.2, C18.2, C19.2, C20.2, C21.2, C22.2, C23.2, C24.2, C25.2, C26.2, C27.2, C28.2, C29.2, C30.2, C31.2, C32.2, C33.2, C34.2, C35.2, C36.2, C37.2, C38.2, U2.8 (DGND), U2.20 (SHDN), U2.22 (DGND), U2.23 (AGNDS), U2.25 (AGND), U2.28 (AGNDS), U2.30 (AGND), U2.32 (AGNDS), U2.36 (AGND), U2.38 (AGNDS), U2.43 (AGNDS), U2.45 (AGND), U2.49 (AGNDS), U2.51 (AGND), U2.53 (AGNDS), U2.56 (AGND), U2.58 (AGNDS), U2.59 (DGND), U2.65 (EP_GND), U3.8 (DGND), U3.20 (SHDN), U3.22 (DGND), U3.23 (AGNDS), U3.25 (AGND), U3.28 (AGNDS), U3.30 (AGND), U3.32 (AGNDS), U3.36 (AGND), U3.38 (AGNDS), U3.43 (AGNDS), U3.45 (AGND), U3.49 (AGNDS), U3.51 (AGND), U3.53 (AGNDS), U3.56 (AGND), U3.58 (AGNDS), U3.59 (DGND), U3.65 (EP_GND); also elsewhere on the board
unnamed: C9.1, U2.41 (REFIO)
unnamed: C10.1, U3.41 (REFIO)
